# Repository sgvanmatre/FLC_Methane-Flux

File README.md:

# Open-source Methane Flux Instrument

Methane, a potent greenhouse gas, has significantly increased in the Earth’s atmosphere since the Industrial Revolution. A considerable portion of methane emissions stems from ground-to-atmosphere methane flux, originating from sources such as landfills, geologic seeps, and agricultural activities. These emissions exhibit spatial complexity and temporal variability, posing challenges in accurate characterization and mitigation.

Quantifying methane flux from these diverse sources is hindered by the lack of affordable measurement tools suitable for widespread deployment. There is a critical need for an instrument capable of measuring flux rates spanning 0.1 to 1000 g CH4 m-2 d-1 at landfills. The ideal instrument must operate autonomously with a remote power supply, and be compact and lightweight enough for easy transport by two individuals. It should provide flux measurements at hourly intervals and support cellular data transmission.

Through a collaborative effort between Fort Lewis College and CU Boulder's air quality laboratories, a low-cost, dynamic flux chamber was developed, calibrated, and validated for measuring methane flux within the range of 0-150 g/m²-day. Methane concentrations in the sensor chamber are monitored using four low-cost metal oxide sensors: a BME 680, along with Figaro TGS sensors (2600, 2602, and 2611).

This repository includes the PCB design and the microcontroller code for the system. 

## Table of Contents

- [Usage](#usage)
- [Contributing](#contributing)
- [Credits](#credits)
- [License](#license)
- [Updating Firmware](#updating-firmware)

## Usage

We encourage everyone to use or adapt this code for their own projects. Below are some examples and instructions to help you get started.

### Tools Used

- **Eagle PCB Software:** We used Eagle PCB software for designing and testing our printed circuit boards.
- **Arduino:** Our code is compatible with the Arduino platform and was developed using the Arduino IDE and initialized on an Arduino MKR NB 1500 board. We did have to manually update the firmware. Instruction are at the bottom of this file.

### Getting Started

1. **Clone the Repository:**
   - Clone the repository to your local machine using the following command:
     ```sh
     git clone https://github.com/your-username/your-repo-name.git
     ```

2. **Open in Eagle PCB Software:**
   - Open the Eagle PCB files from the repository in Eagle PCB software to view and modify the PCB designs.

3. **Load the Code in Arduino IDE:**
   - Open the Arduino IDE.
   - Load the Arduino code from the repository into the Arduino IDE.

4. **Upload to Your Arduino Board:**
   - Connect your Arduino board to your computer.
   - Select the correct board and port from the Arduino IDE.
   - Click the "Upload" button to upload the code to your Arduino board.

## Contributing

We welcome contributions from anyone who is interested! Whether it's fixing a bug, adding a new feature, improving documentation, or any other enhancements, your help is greatly appreciated.

### How to Contribute

1. **Fork the Repository:**
   - Click the "Fork" button at the top right of this repository page to create a copy of this repository in your GitHub account.

2. **Clone Your Fork:**
   - Clone your forked repository to your local machine using the following command:
     ```sh
     git clone https://github.com/your-username/your-repo-name.git
     ```

3. **Create a New Branch:**
   - Create a new branch to work on your changes:
     ```sh
     git checkout -b your-branch-name
     ```

4. **Make Your Changes:**
   - Implement your changes in the new branch.

5. **Commit Your Changes:**
   - Commit your changes with a clear and concise commit message:
     ```sh
     git add .
     git commit -m "Description of your changes"
     ```

6. **Push Your Changes:**
   - Push your changes to your forked repository:
     ```sh
     git push origin your-branch-name
     ```

7. **Submit a Pull Request:**
   - Go to the original repository on GitHub and click the "New Pull Request" button.
   - Select your branch from your forked repository and compare it with the base repository.
   - Submit the pull request for review.

### Guidelines

- Ensure your code follows the project's style guidelines.
- Write clear, concise commit messages.
- Update documentation as necessary.
- Test your changes thoroughly before submitting a pull request.

Thank you for your interest in contributing! Together, we can make this project even better.

## Credits

Contributors

- **Principal Contributor:** [Seth VanMatre](https://github.com/sgvanmatre)
- **Summer Contributions:** [Sonie Taylor Schermer](https://github.com/tschermer02)
- **Additional Assistance:** [Max Krauss](https://github.com/maxtkrauss)

## License

This project is licensed under the MIT License - see the LICENSE file for details.

## Firmware Update Instructions

The latest SARA-R410M-02B firmware (version -04) is now available publicly on the product page:

[Product Page - SARA-R4 Series](https://www.u-blox.com/en/product/sara-r4-series?legacy=Current#Documentation-&-resources)

A direct download to the firmware files is available here:

[Direct Download - Firmware Files](https://content.u-blox.com/sites/default/files/2023-06/SARA-R410M-02B-04-P1-L0000000512A0221-000K00.zip?_ga=2.26117621.998416448.1694721819-824184379.1689262389)

The recommended method is to update via the native USB port of the SARA-R4 module using our Windows tool "EasyFlash".

To download the correct EasyFlash tool, refer to the link in the PCN to the most up-to-date/recommended version in the section "Tools."

A link to the latest (version -04) PCN is available here:

[PCN - Version -04](https://content.u-blox.com/sites/default/files/documents/SARA-R410M-02B-04_PCN_UBX-22005059.pdf)

For updating the firmware, an application note is available here:

[Application Note - Firmware Update](https://www.u-blox.com/sites/default/files/SARA-R4-FW-Update_AppNote_UBX-17049154.pdf)

### Additional Resources for 3rd Party Boards

- **Arduino MKR NB 1500 USB test points:**
  [Forum Discussion](https://forum.arduino.cc/t/firmware-upgrade-for-ublox-sara-r410m-02b-on-the-mkr-nb-1500-2/699292)

- **Particle Boron:**
  [Community Guide](https://community.particle.io/t/how-to-load-ublox-firmware-upgrade-for-sara-r410-lte-on-the-boron/51769)

- **Sparkfun LTE M1 Shield enable USB:**
  [Hookup Guide](https://learn.sparkfun.com/tutorials/lte-cat-m1nb-iot-shield-hookup-guide?_gl=1*pm7rgo*_ga*NDUwNDc5ODYxLjE2OTMyNDMzMjk.*_ga_T369JS7J9N*MTY5NDc5ODg0My4yLjAuMTY5NDc5ODg0My42MC4wLjA.&_ga=2.145880316.975271267.1694798844-450479861.1693243329#USB-interface)

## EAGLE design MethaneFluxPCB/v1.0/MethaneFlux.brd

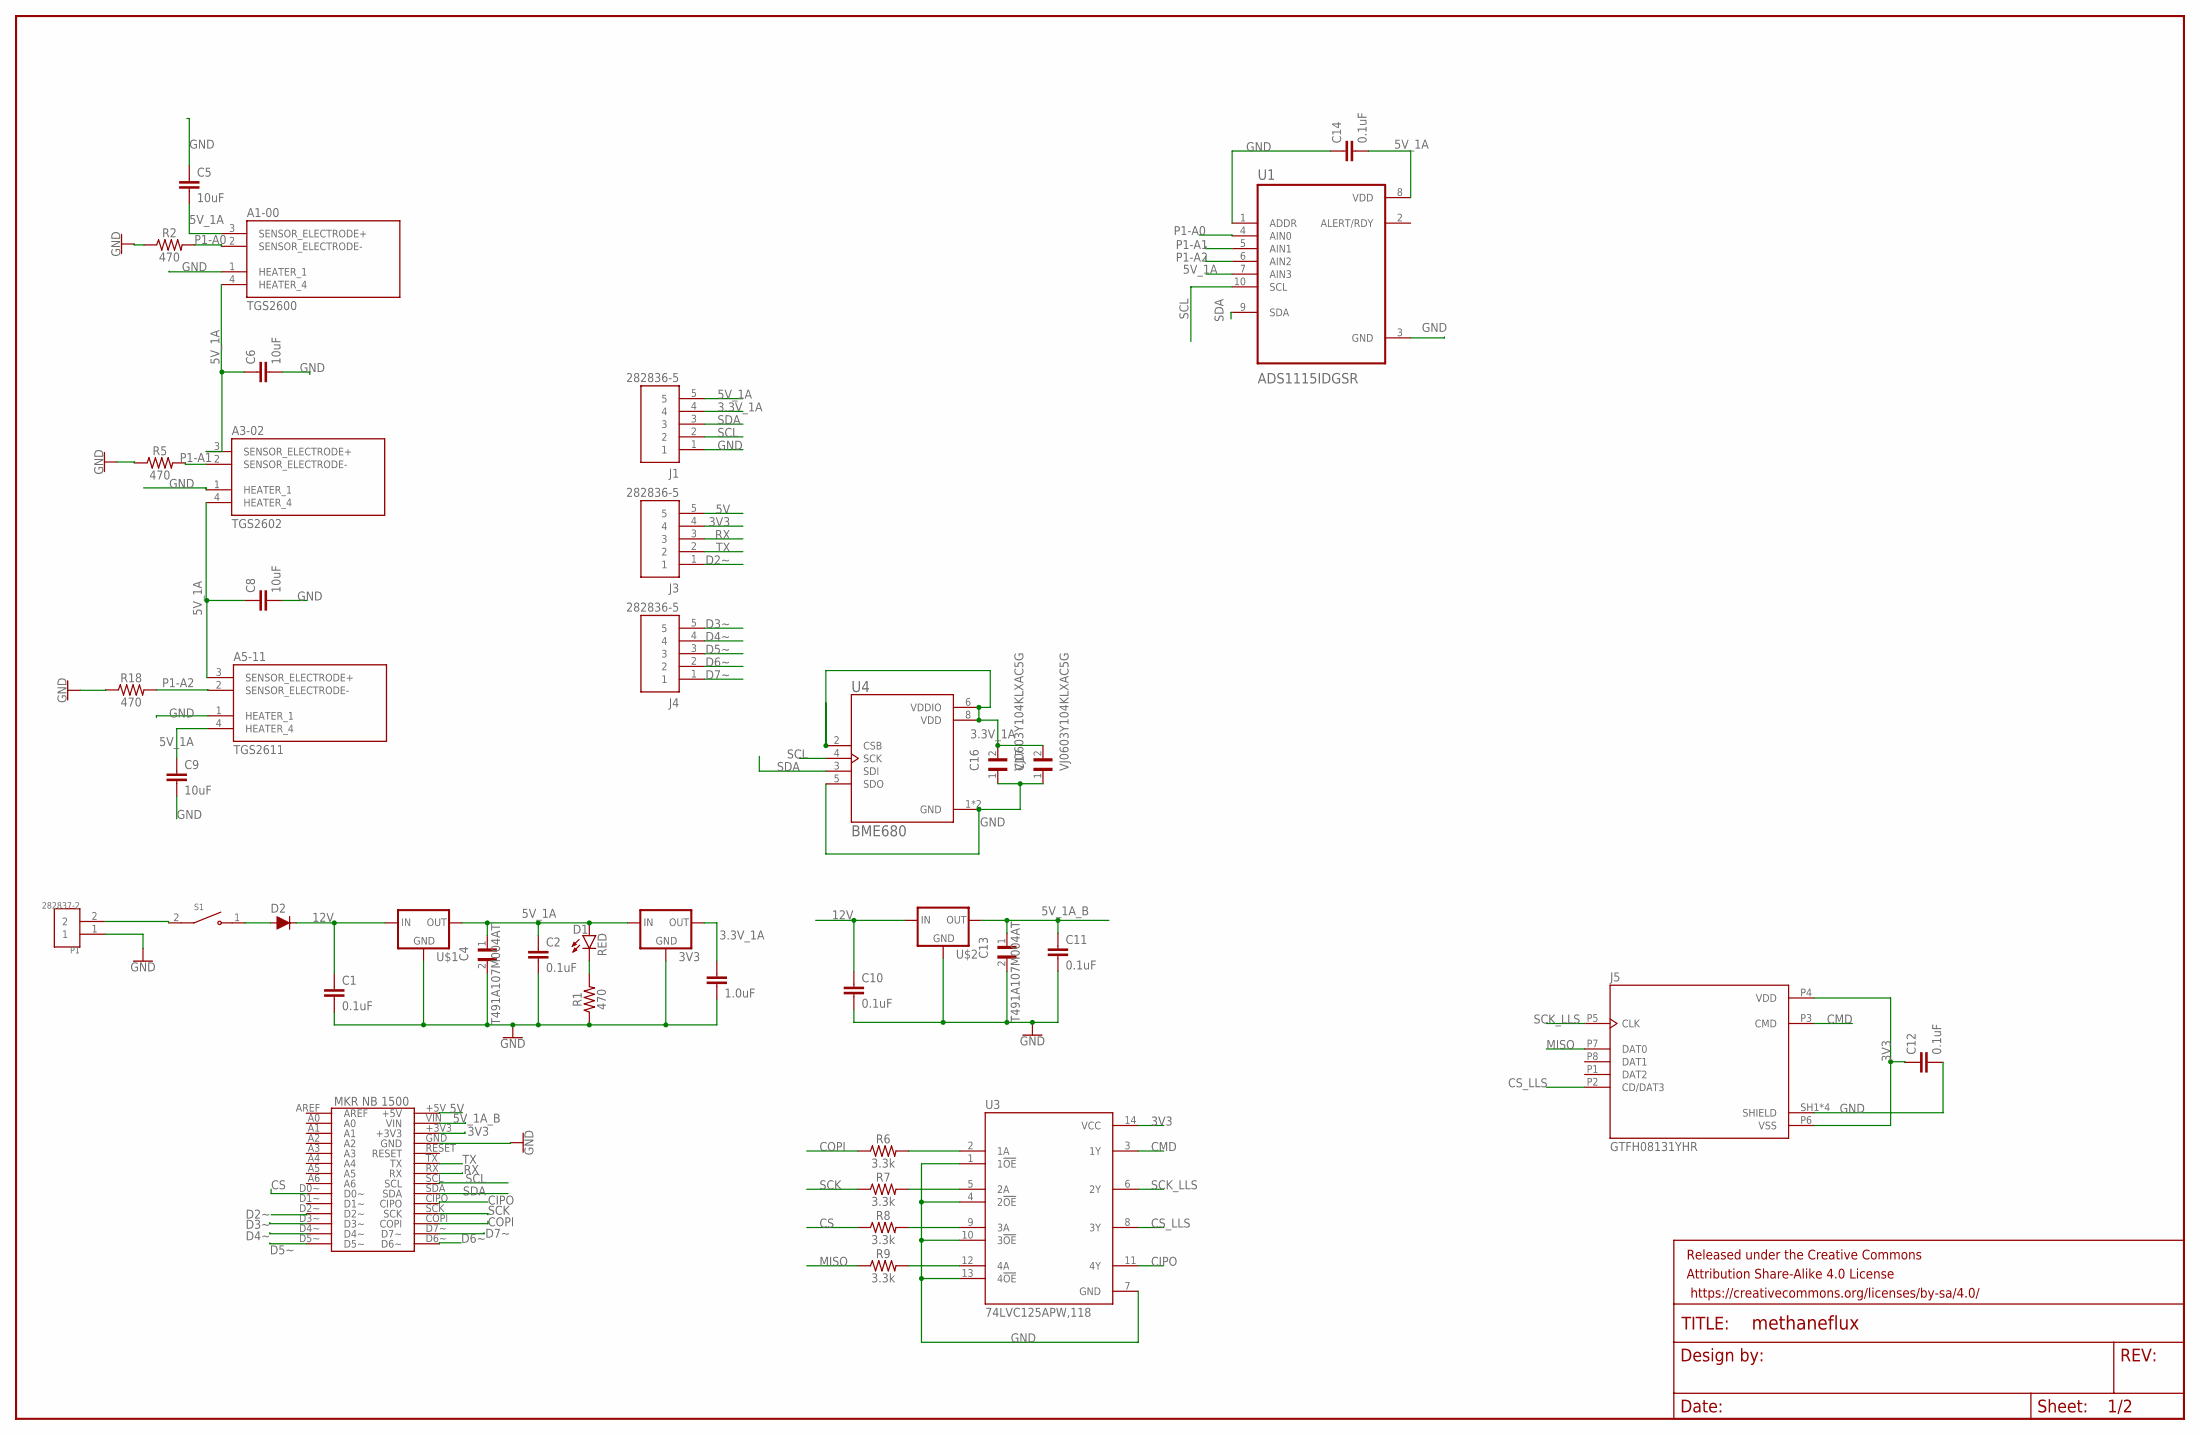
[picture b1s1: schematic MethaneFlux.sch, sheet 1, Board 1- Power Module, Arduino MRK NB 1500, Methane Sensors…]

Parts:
3V3: V_REG_LD1117VXXLD1117-SMD; SOT223
A1-00: TGS2600; TO255P920H830-4
A3-02: TGS2602
A5-11: TGS2611
C1, C2, C10, C11, C12, C14: 0.1uF; 0603
C3: 1.0uF; 0603
C4, C13: T491A107M004AT; CAPC3216X110N
C5, C6, C8, C9: 10uF; 0603
C16, C17: VJ0603Y104KLXAC5G; CAPC1608X92N
D1: RED; LED-0603
D2: 200mA/100V/1V; DIODE-1N4148
FRAME1: FRAME-LEDGER; CREATIVE_COMMONS
J1, J3, J4: 282836-5; TE_282836-5
J5: GTFH08131YHR; AMPHENOL_GTFH08131YHR
P1: 282837-2; TE_282837-2
R1, R2, R5, R18: 470; 0603
R6, R7, R8, R9: 3.3k; 0603
S1: RB141C1100; SW_RB141C1100
U1: ADS1115IDGSR; SOP50P490X110-10N
U3: 74LVC125APW,118; IC_74LVC125APW,118
U4: BME680; PSON80P300X300X100-8N
U$1, U$2: V_REG_LD1117VXXLD1117-SMD; SOT223
U$5: MKRNB1500; MRKNB1500

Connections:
3.3V_1A: 3V3.2 (OUT), C3.1, C16.2, C17.2, J1.4, U4.2 (CSB), U4.6 (VDDIO), U4.8 (VDD)
3V3: C12.1, J3.4, J5.P4 (VDD), J5.P6 (VSS), U3.14 (VCC), U$5.+3V3
5V: J3.5, U$5.+5V
5V_1A: 3V3.3 (IN), A1-00.3 (SENSOR_ELECTRODE+), A1-00.4 (HEATER_4), A3-02.3 (SENSOR_ELECTRODE+), A3-02.4 (HEATER_4), A5-11.3 (SENSOR_ELECTRODE+), A5-11.4 (HEATER_4), C2.1, C4.1, C5.2, C6.1, C8.1, C9.1, C14.2, D1.A, J1.5, U1.7 (AIN3), U1.8 (VDD), U$1.2 (OUT)
5V_1A_B: C11.1, C13.1, U$2.2 (OUT), U$5.VIN
12V: C1.1, C10.1, D2.C, U$1.3 (IN), U$2.3 (IN)
CIPO: U3.11 (4Y), U$5.CIPO
CMD: J5.P3 (CMD), U3.3 (1Y)
COPI: R6.1, U$5.COPI
CS: R8.1, U$5.D0~
CS_LLS: J5.P2 (CD/DAT3), U3.8 (3Y)
D2~: J3.1, U$5.D2~
D3~: J4.5, U$5.D3~
D4~: J4.4, U$5.D4~
D5~: J4.3, U$5.D5~
D6~: J4.2, U$5.D6~
D7~: J4.1, U$5.D7~
GND: 3V3.1 (GND), A1-00.1 (HEATER_1), A3-02.1 (HEATER_1), A5-11.1 (HEATER_1), C1.2, C2.2, C3.2, C4.2, C5.1, C6.2, C8.2, C9.2, C10.2, C11.2, C12.2, C13.2, C14.1, C16.1, C17.1, J1.1, J5.SH1 (SHIELD), J5.SH2 (SHIELD), J5.SH3 (SHIELD), J5.SH4 (SHIELD), P1.1, R1.1, R2.1, R5.1, R18.1, U1.1 (ADDR), U1.3 (GND), U3.1 (1!OE), U3.4 (2!OE), U3.7 (GND), U3.10 (3!OE), U3.13 (4!OE), U4.1 (GND), U4.5 (SDO), U4.7 (GND), U$1.1 (GND), U$2.1 (GND), U$5.GND
MISO: J5.P7 (DAT0), R9.1
unnamed: R6.2, U3.2 (1A)
unnamed: D1.C, R1.2
unnamed: R7.2, U3.5 (2A)
unnamed: P1.2, S1.2
unnamed: D2.A, S1.1
unnamed: R8.2, U3.9 (3A)
unnamed: R9.2, U3.12 (4A)
P1-A0: A1-00.2 (SENSOR_ELECTRODE-), R2.2, U1.4 (AIN0)
P1-A1: A3-02.2 (SENSOR_ELECTRODE-), R5.2, U1.5 (AIN1)
P1-A2: A5-11.2 (SENSOR_ELECTRODE-), R18.2, U1.6 (AIN2)
RX: J3.3, U$5.RX
SCK: R7.1, U$5.SCK
SCK_LLS: J5.P5 (CLK), U3.6 (2Y)
SCL: J1.2, U1.10 (SCL), U4.4 (SCK), U$5.SCL
SDA: J1.3, U1.9 (SDA), U4.3 (SDI), U$5.SDA
TX: J3.2, U$5.TX

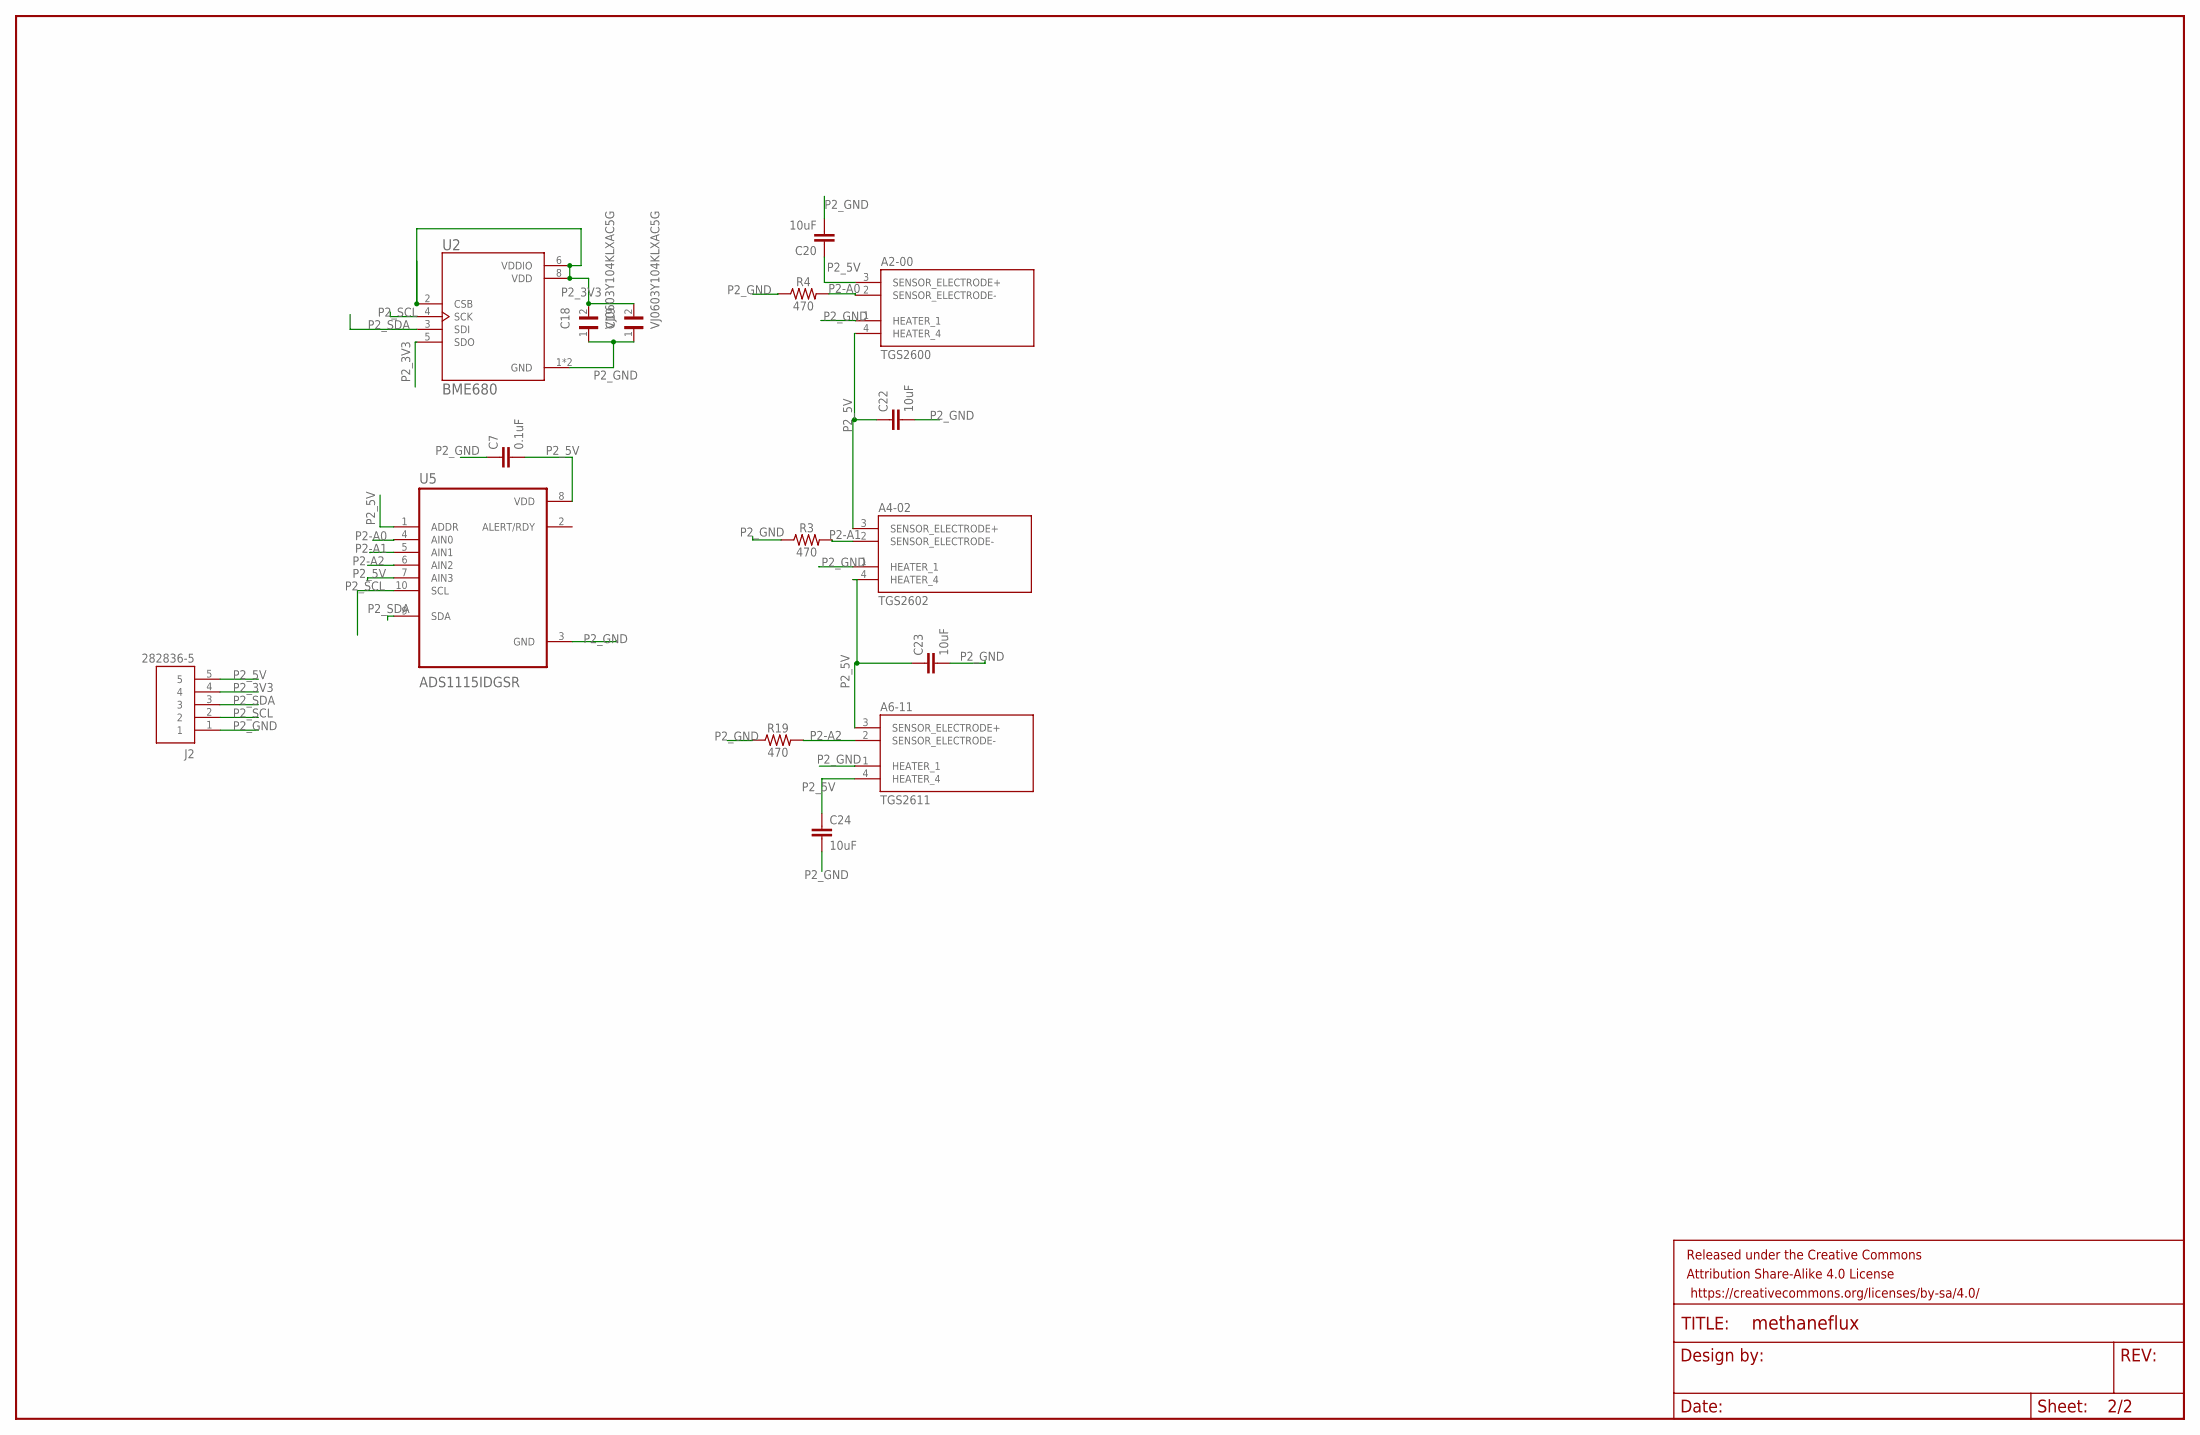
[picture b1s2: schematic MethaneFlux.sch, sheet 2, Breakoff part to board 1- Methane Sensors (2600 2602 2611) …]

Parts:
A2-00: TGS2600; TO255P920H830-4
A4-02: TGS2602
A6-11: TGS2611
C7: 0.1uF; 0603
C18, C19: VJ0603Y104KLXAC5G; CAPC1608X92N
C20, C22, C23, C24: 10uF; 0603
FRAME2: FRAME-LEDGER; CREATIVE_COMMONS
J2: 282836-5; TE_282836-5
R3, R4, R19: 470; 0603
U2: BME680; PSON80P300X300X100-8N
U5: ADS1115IDGSR; SOP50P490X110-10N

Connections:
P2-A0: A2-00.2 (SENSOR_ELECTRODE-), R4.2, U5.4 (AIN0)
P2-A1: A4-02.2 (SENSOR_ELECTRODE-), R3.2, U5.5 (AIN1)
P2-A2: A6-11.2 (SENSOR_ELECTRODE-), R19.2, U5.6 (AIN2)
P2_3V3: C18.2, C19.2, J2.4, U2.2 (CSB), U2.5 (SDO), U2.6 (VDDIO), U2.8 (VDD)
P2_5V: A2-00.3 (SENSOR_ELECTRODE+), A2-00.4 (HEATER_4), A4-02.3 (SENSOR_ELECTRODE+), A4-02.4 (HEATER_4), A6-11.3 (SENSOR_ELECTRODE+), A6-11.4 (HEATER_4), C7.2, C20.1, C22.1, C23.1, C24.1, J2.5, U5.1 (ADDR), U5.7 (AIN3), U5.8 (VDD)
P2_GND: A2-00.1 (HEATER_1), A4-02.1 (HEATER_1), A6-11.1 (HEATER_1), C7.1, C18.1, C19.1, C20.2, C22.2, C23.2, C24.2, J2.1, R3.1, R4.1, R19.1, U2.1 (GND), U2.7 (GND), U5.3 (GND)
P2_SCL: J2.2, U2.4 (SCK), U5.10 (SCL)
P2_SDA: J2.3, U2.3 (SDI), U5.9 (SDA)

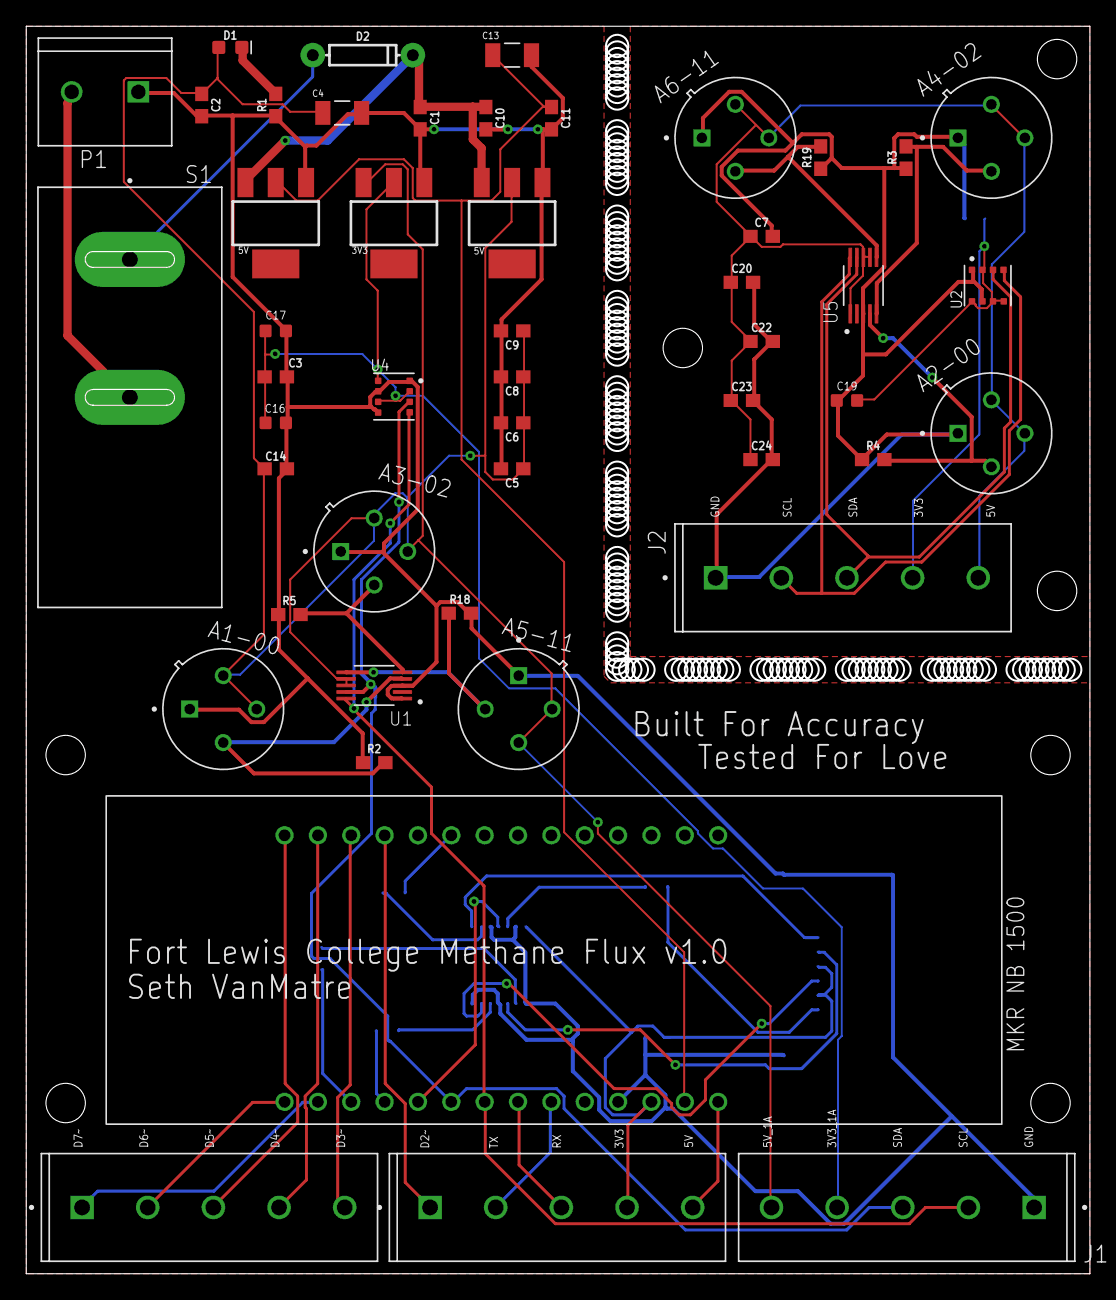
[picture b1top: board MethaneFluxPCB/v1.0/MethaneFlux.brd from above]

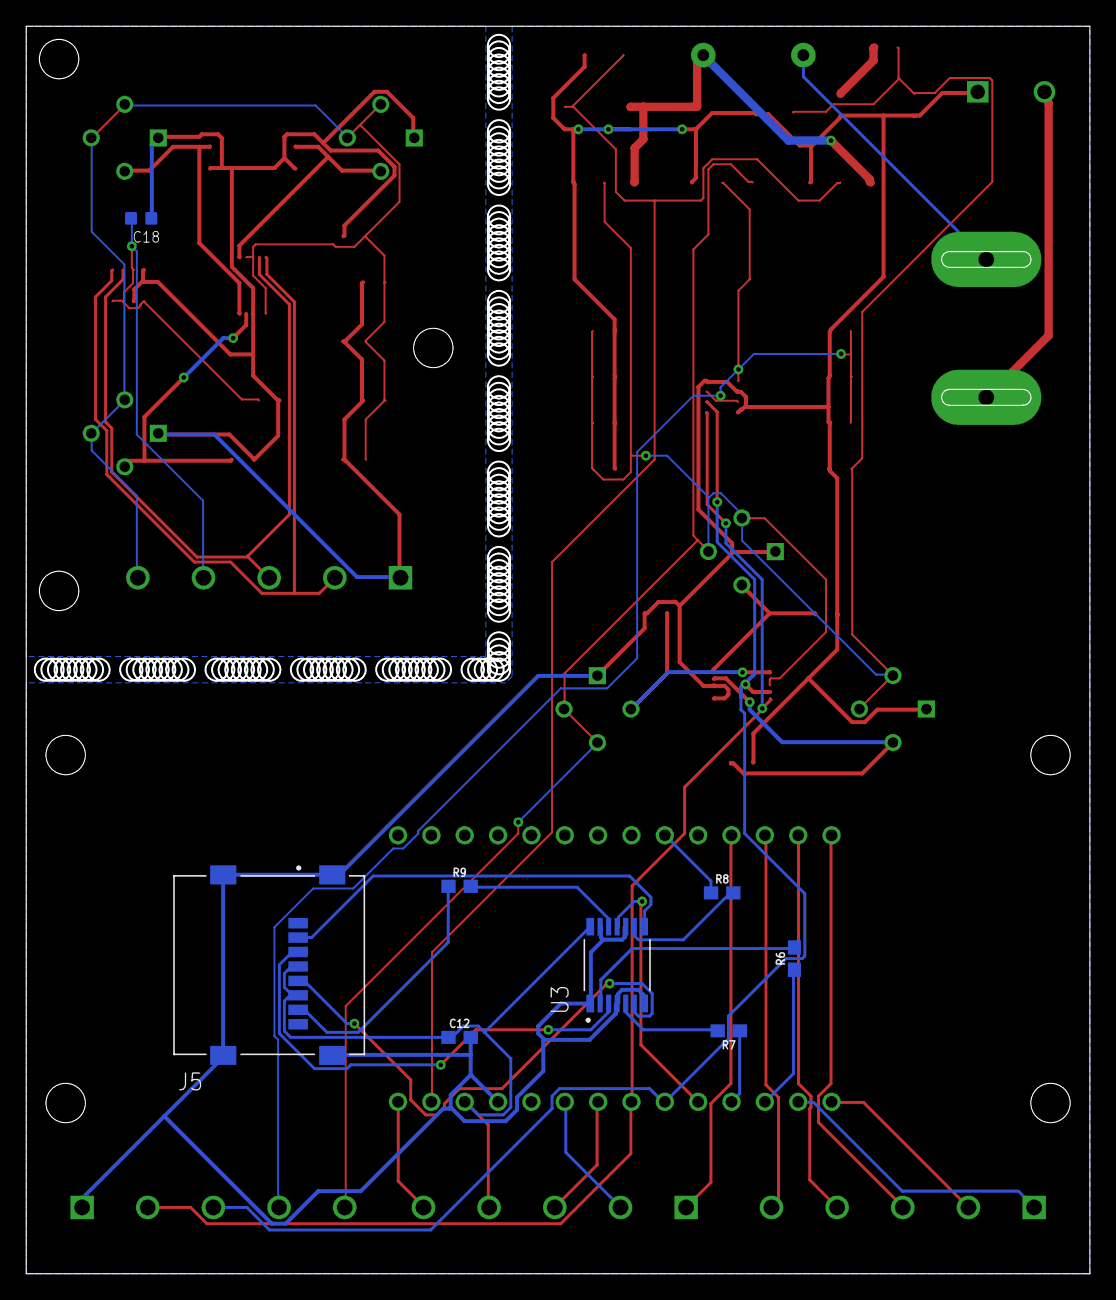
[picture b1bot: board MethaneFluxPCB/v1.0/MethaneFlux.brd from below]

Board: 2 copper layers, 80.8 x 94.8 mm, 59 parts (8 on the bottom side), 43 nets.

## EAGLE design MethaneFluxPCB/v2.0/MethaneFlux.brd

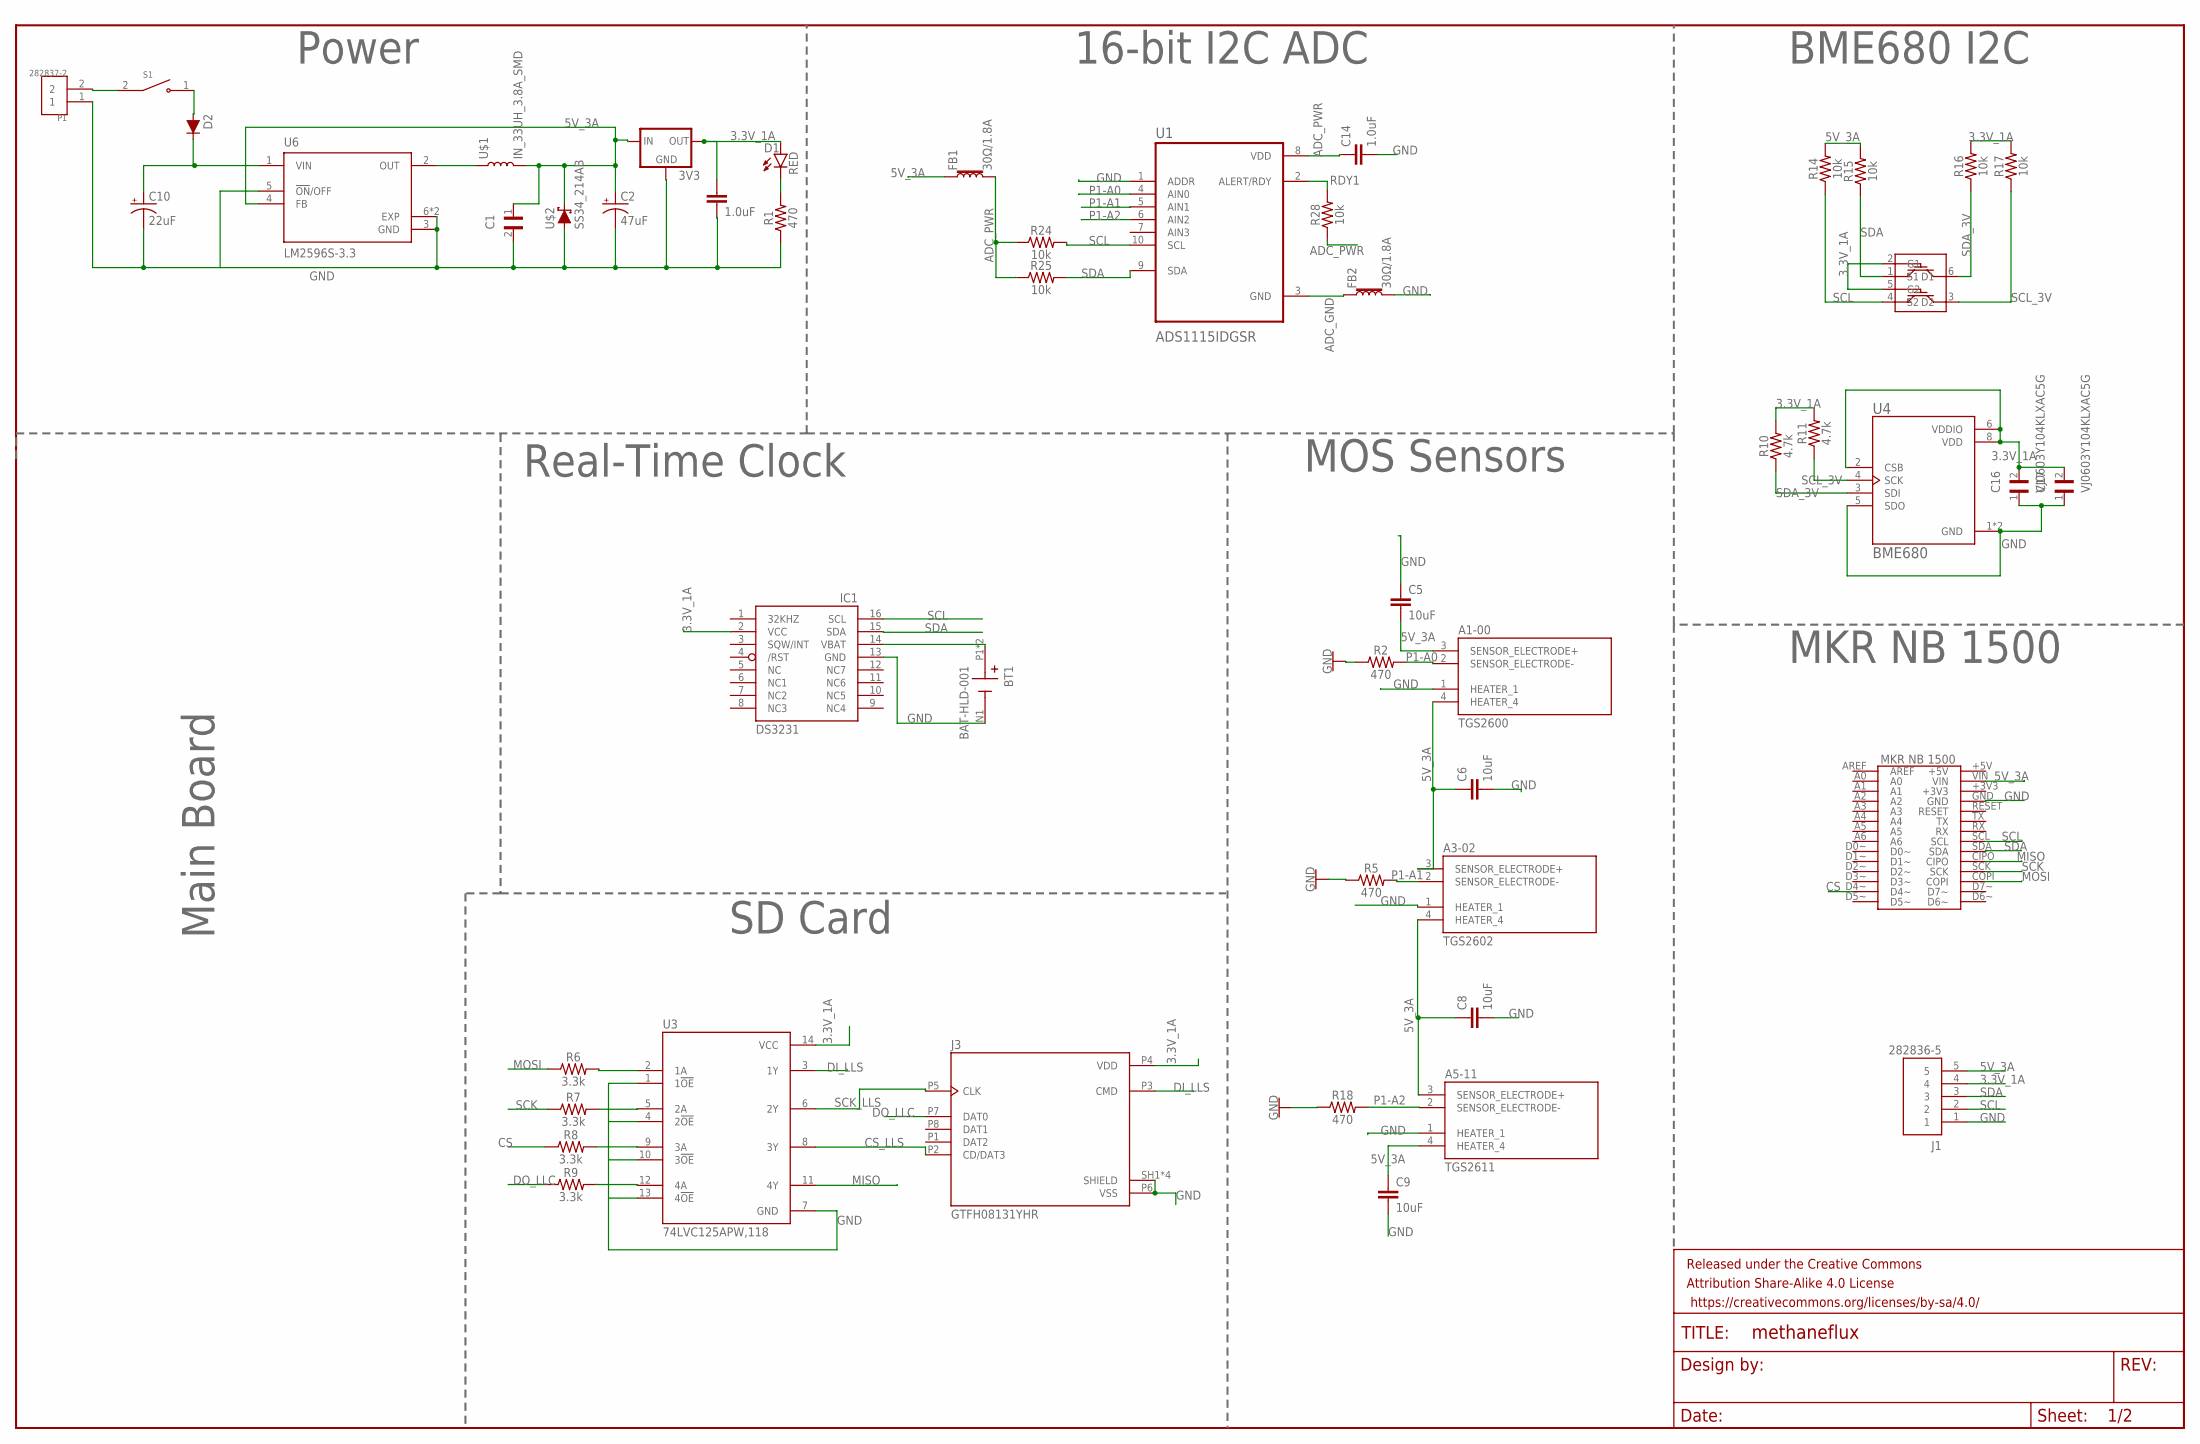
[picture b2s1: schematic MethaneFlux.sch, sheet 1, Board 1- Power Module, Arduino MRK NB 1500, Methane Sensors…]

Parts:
3V3: V_REG_LD1117VXXLD1117-SMD; SOT223
A1-00: TGS2600; TO255P920H830-4
A3-02: TGS2602
A5-11: TGS2611
BT1: BAT-HLD-001; BAT_BAT-HLD-001
C1: T491A107M004AT; CAPC3216X110N
C2: 47uF; PANASONIC_D
C3, C14: 1.0uF; 0603
C5, C6, C8, C9: 10uF; 0603
C10: 22uF; PANASONIC_C
C16, C17: VJ0603Y104KLXAC5G; CAPC1608X92N
D1: RED; LED-0603
D2: 200mA/100V/1V; DIODE-1N4148
FB1, FB2: 30Ω/1.8A; 0603
FRAME1: FRAME-LEDGER; CREATIVE_COMMONS
IC1: DS3231/SO; SO16W
J1: 282836-5; TE_282836-5
J3: GTFH08131YHR; AMPHENOL_GTFH08131YHR
P1: 282837-2; TE_282837-2
R1, R2, R5, R18: 470; 0603
R6, R7, R8, R9: 3.3k; 0603
R10, R11: 4.7k; 0603
R14, R15, R16, R17, R24, R25, R28: 10k; 0603
S1: RB141C1100; SW_RB141C1100
U1: ADS1115IDGSR; SOP50P490X110-10N
U3: 74LVC125APW,118; IC_74LVC125APW,118
U4: BME680; PSON80P300X300X100-8N
U6: LM2596S-3.3; VREG_LM2596S-3.3
U$1: IN_33UH_3.8A_SMD; INDUCTOR_4X4MM
U$2: SS34_214AB; SOD-323
U$3: 2N7002DW; SOT363
U$5: MKRNB1500; MRKNB1500

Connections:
3.3V_1A: 3V3.2 (OUT), C3.1, C16.2, C17.2, D1.A, IC1.2 (VCC), J1.4, J3.P4 (VDD), R10.2, R11.2, R16.2, R17.2, U3.14 (VCC), U4.2 (CSB), U4.6 (VDDIO), U4.8 (VDD), U$3.2 (G1), U$3.5 (G2)
5V_3A: 3V3.3 (IN), A1-00.3 (SENSOR_ELECTRODE+), A1-00.4 (HEATER_4), A3-02.3 (SENSOR_ELECTRODE+), A3-02.4 (HEATER_4), A5-11.3 (SENSOR_ELECTRODE+), A5-11.4 (HEATER_4), C1.1, C2.+, C5.2, C6.1, C8.1, C9.1, FB1.1, J1.5, R14.2, R15.2, U6.4 (FB), U$1.P$2 (2), U$2.C, U$5.VIN
ADC_GND: FB2.1, U1.3 (GND)
ADC_PWR: C14.1, FB1.2, R24.1, R25.1, R28.1, U1.8 (VDD)
CS: R8.1, U$5.D4~
CS_LLS: J3.P2 (CD/DAT3), U3.8 (3Y)
DI_LLS: J3.P3 (CMD), U3.3 (1Y)
DO_LLC: J3.P7 (DAT0), R9.1
GND: 3V3.1 (GND), A1-00.1 (HEATER_1), A3-02.1 (HEATER_1), A5-11.1 (HEATER_1), BT1.N1 (-), C1.2, C2.-, C3.2, C5.1, C6.2, C8.2, C9.2, C10.-, C14.2, C16.1, C17.1, FB2.2, IC1.13 (GND), J1.1, J3.P6 (VSS), J3.SH1 (SHIELD), J3.SH2 (SHIELD), J3.SH3 (SHIELD), J3.SH4 (SHIELD), P1.1, R1.1, R2.1, R5.1, R18.1, U1.1 (ADDR), U3.1 (1!OE), U3.4 (2!OE), U3.7 (GND), U3.10 (3!OE), U3.13 (4!OE), U4.1 (GND), U4.5 (SDO), U4.7 (GND), U6.3 (GND), U6.5 (!ON!/OFF), U6.6 (EXP), U6.7 (EXP), U$2.A, U$5.GND
MISO: U3.11 (4Y), U$5.CIPO
MOSI: R6.1, U$5.COPI
unnamed: R6.2, U3.2 (1A)
unnamed: P1.2, S1.2
unnamed: D2.A, S1.1
unnamed: R7.2, U3.5 (2A)
unnamed: R8.2, U3.9 (3A)
unnamed: R9.2, U3.12 (4A)
unnamed: U6.2 (OUT), U$1.P$1 (1)
unnamed: BT1.P1 (+), BT1.P2 (+), IC1.14 (VBAT)
unnamed: C10.+, D2.C, U6.1 (VIN)
unnamed: D1.C, R1.2
P1-A0: A1-00.2 (SENSOR_ELECTRODE-), R2.2, U1.4 (AIN0)
P1-A1: A3-02.2 (SENSOR_ELECTRODE-), R5.2, U1.5 (AIN1)
P1-A2: A5-11.2 (SENSOR_ELECTRODE-), R18.2, U1.6 (AIN2)
RDY1: R28.2, U1.2 (ALERT/RDY)
SCK: R7.1, U$5.SCK
SCK_LLS: J3.P5 (CLK), U3.6 (2Y)
SCL: IC1.16 (SCL), J1.2, R14.1, R24.2, U1.10 (SCL), U$3.4 (S2), U$5.SCL
SCL_3V: R11.1, R17.1, U4.4 (SCK), U$3.3 (D2)
SDA: IC1.15 (SDA), J1.3, R15.1, R25.2, U1.9 (SDA), U$3.1 (S1), U$5.SDA
SDA_3V: R10.1, R16.1, U4.3 (SDI), U$3.6 (D1)

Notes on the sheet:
MKR NB 1500
MOS Sensors
BME680 I2C
16-bit I2C ADC
Power
Real-Time Clock
SD Card
Main Board

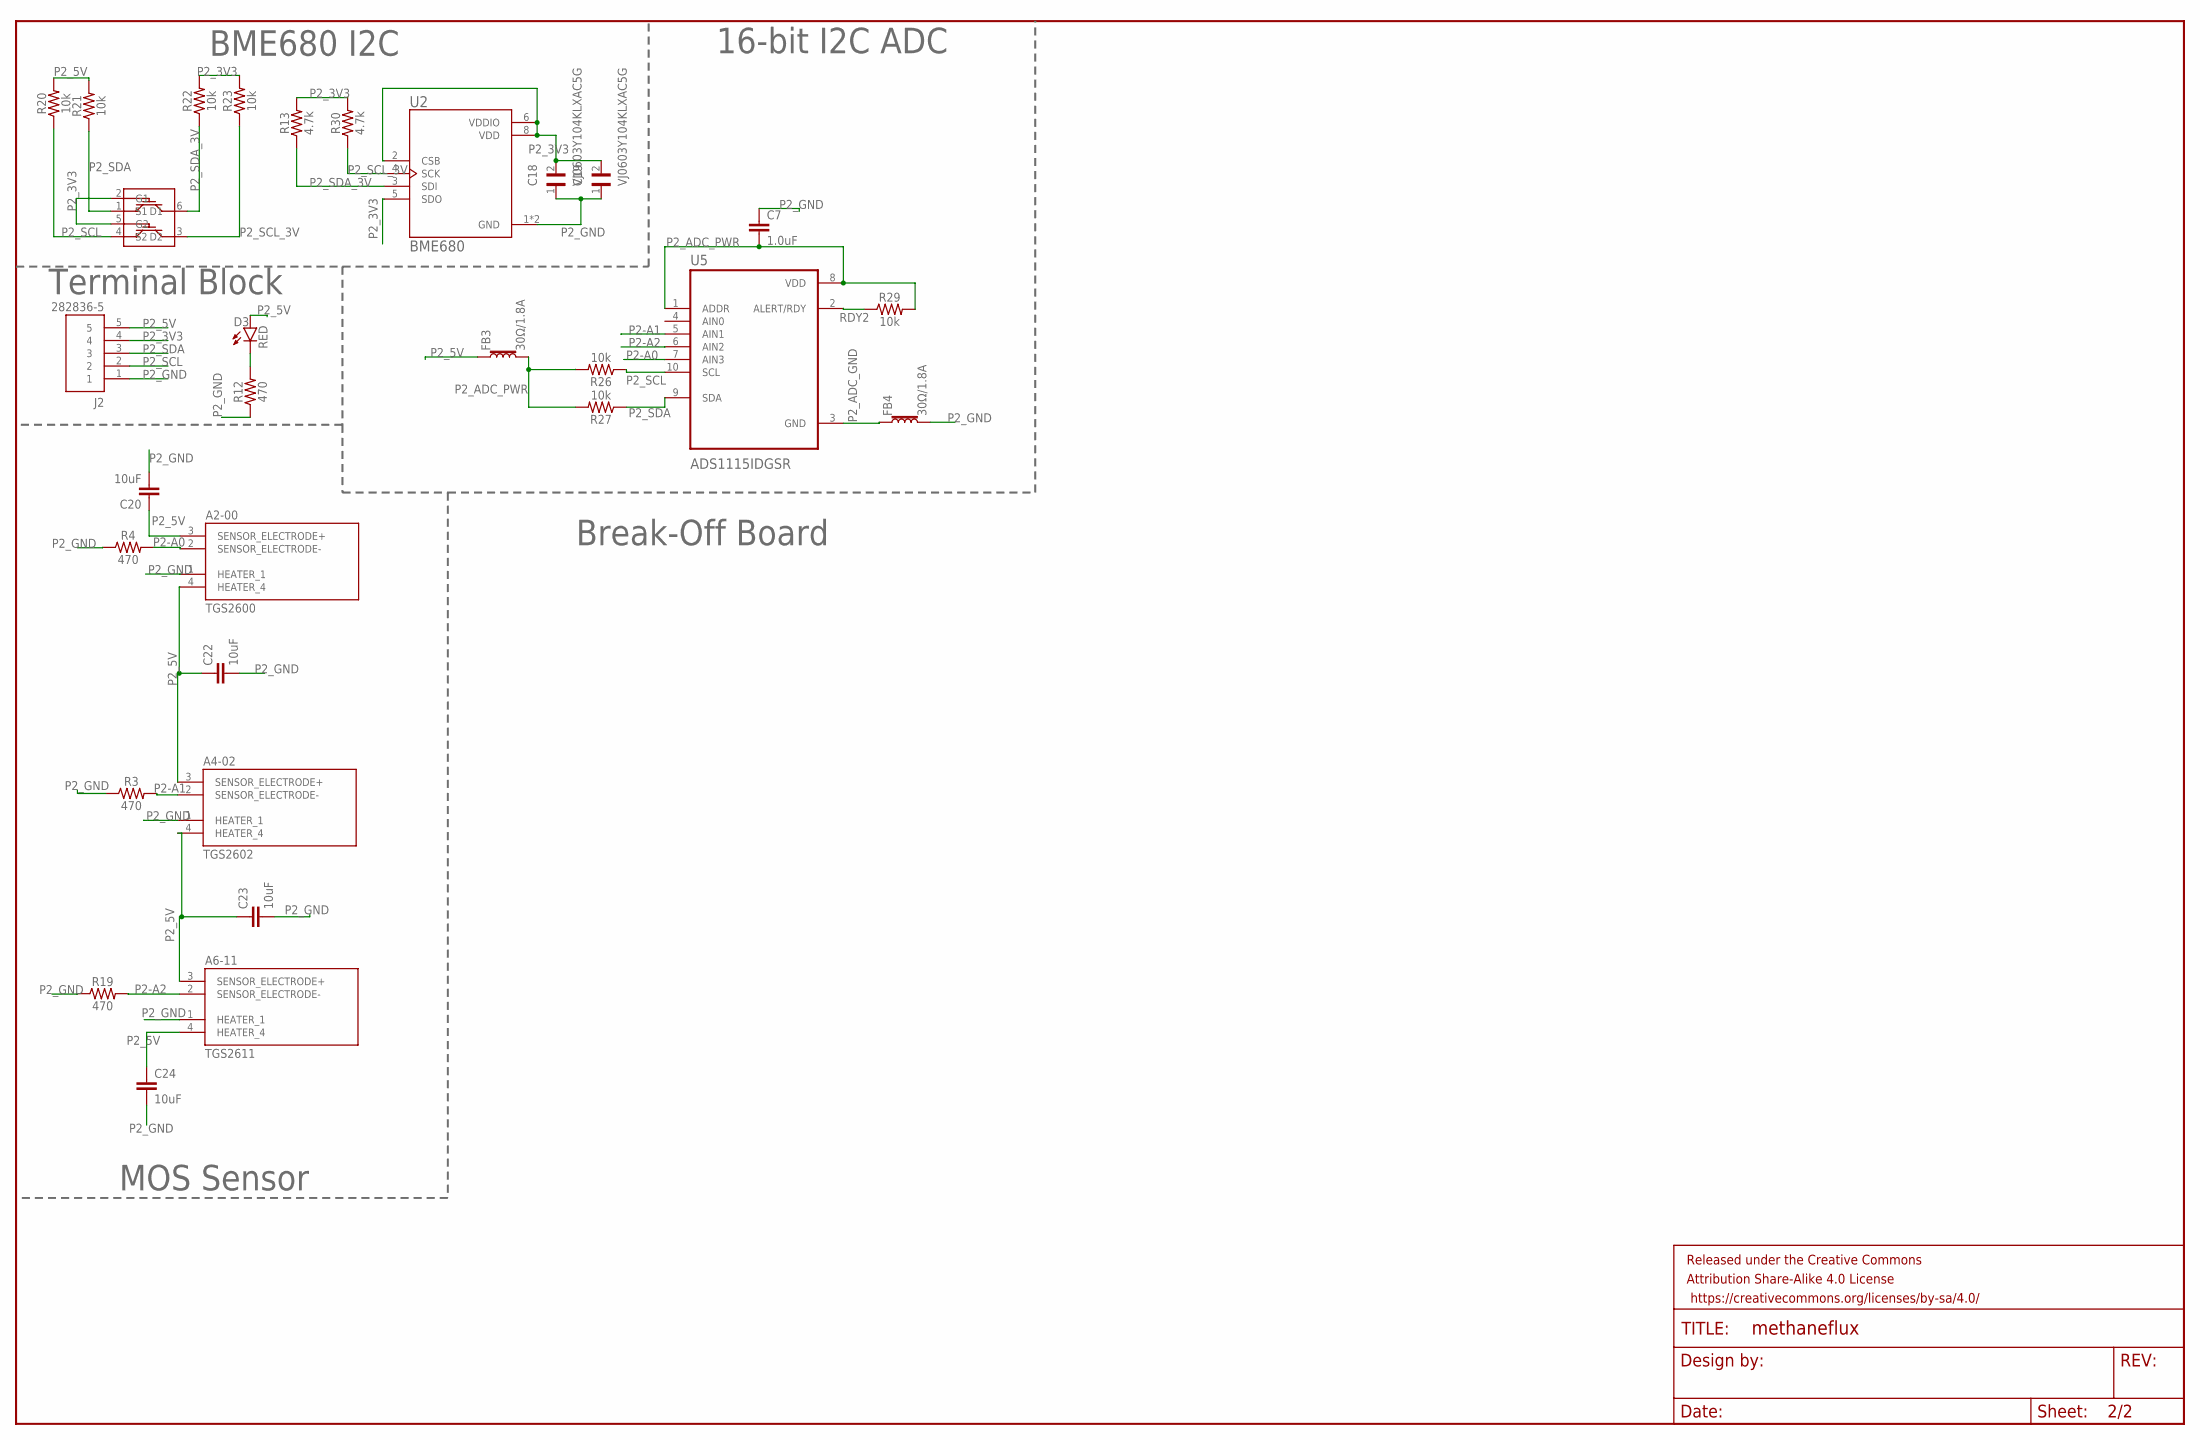
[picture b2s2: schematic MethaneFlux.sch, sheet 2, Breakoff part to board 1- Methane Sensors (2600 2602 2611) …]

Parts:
A2-00: TGS2600; TO255P920H830-4
A4-02: TGS2602
A6-11: TGS2611
C7: 1.0uF; 0603
C18, C19: VJ0603Y104KLXAC5G; CAPC1608X92N
C20, C22, C23, C24: 10uF; 0603
D3: RED; LED-0603
FB3, FB4: 30Ω/1.8A; 0603
FRAME2: FRAME-LEDGER; CREATIVE_COMMONS
J2: 282836-5; TE_282836-5
R3, R4, R12, R19: 470; 0603
R13, R30: 4.7k; 0603
R20, R21, R22, R23, R26, R27, R29: 10k; 0603
U2: BME680; PSON80P300X300X100-8N
U5: ADS1115IDGSR; SOP50P490X110-10N
U$4: 2N7002DW; SOT363

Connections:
unnamed: D3.C, R12.2
P2-A0: A2-00.2 (SENSOR_ELECTRODE-), R4.2, U5.7 (AIN3)
P2-A1: A4-02.2 (SENSOR_ELECTRODE-), R3.2, U5.5 (AIN1)
P2-A2: A6-11.2 (SENSOR_ELECTRODE-), R19.2, U5.6 (AIN2)
P2_3V3: C18.2, C19.2, J2.4, R13.2, R22.2, R23.2, R30.2, U2.2 (CSB), U2.5 (SDO), U2.6 (VDDIO), U2.8 (VDD), U$4.2 (G1), U$4.5 (G2)
P2_5V: A2-00.3 (SENSOR_ELECTRODE+), A2-00.4 (HEATER_4), A4-02.3 (SENSOR_ELECTRODE+), A4-02.4 (HEATER_4), A6-11.3 (SENSOR_ELECTRODE+), A6-11.4 (HEATER_4), C20.1, C22.1, C23.1, C24.1, D3.A, FB3.1, J2.5, R20.2, R21.2
P2_ADC_GND: FB4.1, U5.3 (GND)
P2_ADC_PWR: C7.2, FB3.2, R26.2, R27.2, R29.2, U5.1 (ADDR), U5.8 (VDD)
P2_GND: A2-00.1 (HEATER_1), A4-02.1 (HEATER_1), A6-11.1 (HEATER_1), C7.1, C18.1, C19.1, C20.2, C22.2, C23.2, C24.2, FB4.2, J2.1, R3.1, R4.1, R12.1, R19.1, U2.1 (GND), U2.7 (GND)
P2_SCL: J2.2, R20.1, R26.1, U5.10 (SCL), U$4.4 (S2)
P2_SCL_3V: R23.1, R30.1, U2.4 (SCK), U$4.3 (D2)
P2_SDA: J2.3, R21.1, R27.1, U5.9 (SDA), U$4.1 (S1)
P2_SDA_3V: R13.1, R22.1, U2.3 (SDI), U$4.6 (D1)
RDY2: R29.1, U5.2 (ALERT/RDY)

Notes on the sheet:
MOS Sensor
Terminal Block
BME680 I2C
16-bit I2C ADC
Break-Off Board

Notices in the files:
parts and their libraries:
SparkFun-Capacitors: Licensing: Creative Commons ShareAlike 4.0 International - https://creativecommons.org/licenses/by-sa/4.0
SparkFun-Aesthetics: Released under the Creative Commons Attribution Share-Alike 4.0 License
SparkFun-Aesthetics: https://creativecommons.org/licenses/by-sa/4.0
